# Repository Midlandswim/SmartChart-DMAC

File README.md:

# SmartChart & DMAC Research
SmartChart Patient Charting App and the Deployable Medical Assistance Case

Researcher: Wilson Dhalwani & Giacomo Pugliese <br />
Advisors: Mr. Michael Liva (BCA) & Mr. Joseph Barbetta (BCA) & Mr. Oliver Dobrich (BCA) & Ms. Clare Kennedy (BCA) <br />
Context: Future Health Professionals (HOSA) International Leadership Conference Medical Innovation <br />
Project Name: SmartChart & Deployable Medical Assistance Case <br />
Start Date: April 04, 2023 <br />

The following repository is for documenting and sharing my work in this research competition and its related fields of engineering and medicine. This was also made for recording my process of solving the issue at hand so that others can learn and build upon my work. An award-winning software that is the most intelligent and efficient virtual patient charting application for emergency medical technicians on the market, SmartChart utilizes an algorithm that suggests treatment based on patient information. A machine learning model provides diagnostics and appropriate protocols, and more. SmartChart supports audio transcription and translation for patient charting and communication, as well as OCR for written notes. The DMAC was made for our entry into the Medical Innovations Category at HOSA ILC. The team previously won 1st place at the HOSA New Jersey State Conference for Medical Innovation, allowing us to qualify for HOSA ILC in Dallas, TX, in 2023. I was not officially a member of the team during this time, only joining after their accomplishment at the New Jersey State Conference due to scheduling conflicts keeping me from joining the team in an official capacity prior to ILC Qualification. This is why I acted as an unofficial engineering consultant for the project up until the end of the New Jersey State Conference. We finished as semifinalists at HOSA ILC 2023, placing in the top 40 teams in the World. This was done in a team consisting of Giacomo Pugliese, Andrea Kim, and myself. I was the engineer in the group and personally designed the entire DMAC environment, including the aesthetics, custom enclosures, device programming, and solar power systems. The goal of this project is to work in concert with SmartChart, using AI to process and collect data to diagnose and treat patients. Used by EMTs, the DMAC and SmartChart will help revolutionize emergency patient care. This project is also patent pending, with the team recently being granted a provisional utility patent for the entire system. This project has no end date as an innovation never ends, rather, continues until the idea is forgotten, and my hope is that this work can be the basis for future engineers who, too, find great excitement in innovation and design. Featured by multiple news outlets. 
Here is the link to one by Yahoo Finance: https://finance.yahoo.com/video/students-design-smartchart-app-help-195534932.html?guccounter=1 <br />

<p align="center"> <strong> Promotional Video: </strong> </p> 

https://github.com/Midlandswim/SmartChart-DMAC/assets/87616332/fc35b12c-a720-4e8d-b312-f2718276814c

<br />

Should you have any questions, comments, or just wish to reach out, email me at wilson.dhalwani@gmail.com !

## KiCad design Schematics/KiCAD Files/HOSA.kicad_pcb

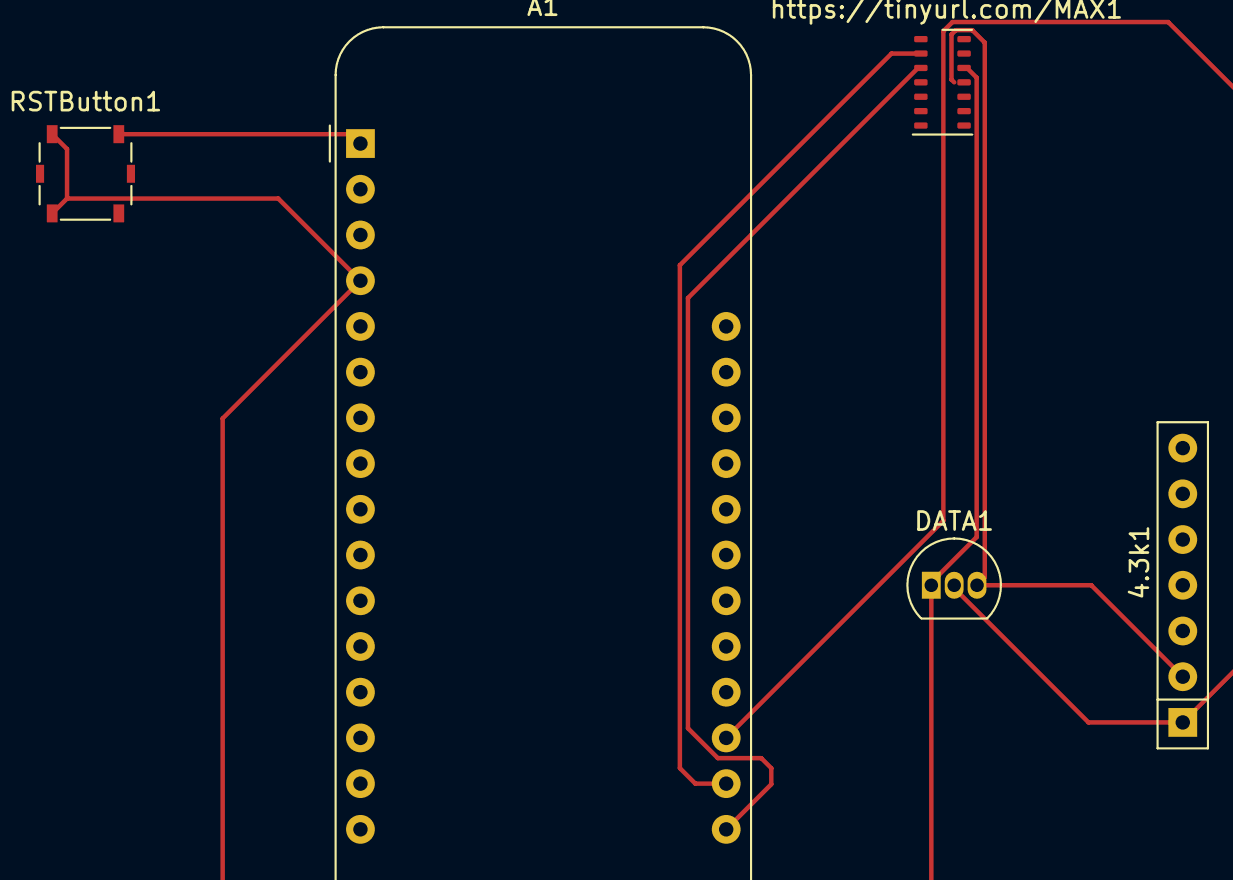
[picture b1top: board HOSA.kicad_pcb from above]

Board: 2 copper layers, 5 parts (0 on the bottom side), 6 nets.

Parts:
4.3k1: 4.3kΩ; R_Array_SIP7
A1: Adafruit_Feather_HUZZAH32_ESP32_V2; Adafruit_Feather
DATA1: DS18B20; TO-92_Inline
RSTButton1: SW_Push; SW_SPST_Panasonic_EVQPL_3PL_5PL_PT_A08
https://tinyurl.com/MAX1: GY-MAX30102; Maxim_OLGA-14_3.3x5.6mm_P0.8mm

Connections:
unnamed: A1.1 (RST), RSTButton1.2
unnamed: 4.3k1.2, A1.2 (3V), DATA1.3 (VDD), https://tinyurl.com/MAX1.11 (VIN)
unnamed: A1.4 (GND), DATA1.1 (GND), RSTButton1.1, https://tinyurl.com/MAX1.12 (GND)
unnamed: A1.17 (SDA/22), https://tinyurl.com/MAX1.3 (SDA)
unnamed: A1.18 (SCL/20), https://tinyurl.com/MAX1.2 (SCL)
unnamed: 4.3k1.1, A1.19 (A6/14), DATA1.2 (DQ)

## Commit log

2023-05-15 SmartChart Website and AI Code
    Created and programmed by Giacomo Pugliese, downloaded and attached here for reference.
2023-05-15 Screw CAD for Solar Charger Enclosure
    Not Made by myself, borrowed from online, no credit to me for these.
2023-05-15 Custom CAD Solar Charger Board
    Made by me
2023-05-15 Custom CAD GY-MAX30102 Board
    Made by me
2023-05-15 Custom CAD Enclosure Wall Designs
    These were made by me. They are installed in a separate custom enclosure.
2023-05-15 Datasheets for Various Related Components
    These are mainly for TSA... haha
2023-05-15 Custom CAD Pulse Oximeter Clip
    Made by me. Inspired by https://www.thingiverse.com/thing:4847827
2023-05-15 Custom CAD MCP73871 Enclosure
    Made by me. The exception is the screws used. The Accyrlic Cover is not meant to be printed, but rather for reference.
2023-05-15 Custom Renders
    Done in Fusion360
2023-05-15 Various Images and Photos
    Tis' done.
2023-05-15 Create SmartChart Reference
2023-05-15 Some useful Links
    A Linkbank, more to be added later
2023-06-13 Internal Electronics for DMAC Processing Enclosure
    Sorry guys, it's messy, really messy (I know). The ultimate shame of any electrical engineering student.... but hey- we have pretty enclosures for a reason! To hide the shame, we hope no one will eve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
2023-06-27 Update SmartChart Reference
2023-06-27 Create Code V1
2023-08-29 Engineering Schematics
    These were also submitted for Patent
2023-08-29 Bad Schematic
    Put it here for fun. Not for any reference or actual use.
2023-08-29 KiCad Schematics
    Newer Version. Made some improvements
2023-08-29 PCB Iteration 1
    The first PCB Design
2023-08-29 First PCB Design
    Iteration 1, done in KiCAD
